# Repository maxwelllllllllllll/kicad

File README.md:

# kicad
 
Here's my dumb repo for projects I'm working on in Kicad. For the near term (and maybe forever), this is going to be entirely custom keyboard projects.

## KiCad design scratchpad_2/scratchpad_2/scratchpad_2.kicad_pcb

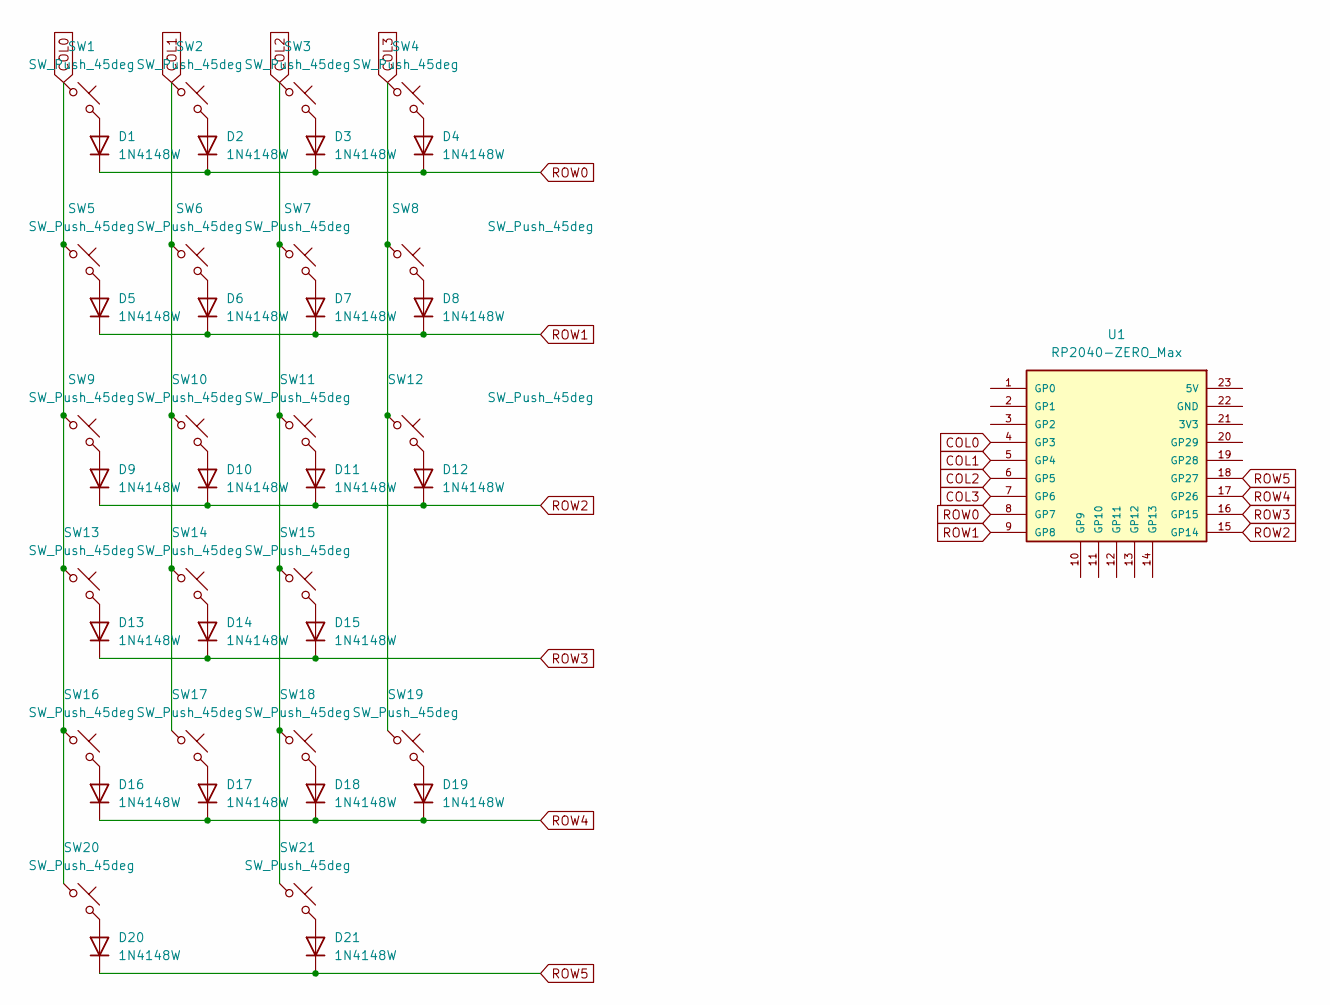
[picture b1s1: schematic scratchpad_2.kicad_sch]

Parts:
D1, D2, D3, D4, D5, D6, D7, D8, D9, D10, D11, D12, D13, D14, D15, D16, D17, D18, D19, D20, D21: 1N4148W; D_SOD-123
SW1, SW2, SW3, SW4, SW5, SW6, SW7, SW8, SW9, SW10, SW11, SW13, SW14, SW15, SW16, SW17, SW18, SW21: SW_Push_45deg; MX-Hotswap-1U
SW12, SW19, SW20: SW_Push_45deg; MX-Hotswap-2U-ReversedStabilizers
U1: RP2040-ZERO_Max; MODULE_RP2040-ZERO

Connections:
COL0: SW1.1, SW5.1, SW9.1, SW13.1, SW16.1, SW20.1, U1.4 (GP3)
COL1: SW2.1, SW6.1, SW10.1, SW14.1, SW17.1, U1.5 (GP4)
COL2: SW3.1, SW7.1, SW11.1, SW15.1, SW18.1, SW21.1, U1.6 (GP5)
COL3: SW4.1, SW8.1, SW12.1, SW19.1, U1.7 (GP6)
unnamed: D1.2 (A), SW1.2
unnamed: D2.2 (A), SW2.2
unnamed: D3.2 (A), SW3.2
unnamed: D4.2 (A), SW4.2
unnamed: D5.2 (A), SW5.2
unnamed: D6.2 (A), SW6.2
unnamed: D7.2 (A), SW7.2
unnamed: D8.2 (A), SW8.2
unnamed: D9.2 (A), SW9.2
unnamed: D10.2 (A), SW10.2
unnamed: D11.2 (A), SW11.2
unnamed: D12.2 (A), SW12.2
unnamed: D13.2 (A), SW13.2
unnamed: D14.2 (A), SW14.2
unnamed: D15.2 (A), SW15.2
unnamed: D16.2 (A), SW16.2
unnamed: D17.2 (A), SW17.2
unnamed: D18.2 (A), SW18.2
unnamed: D19.2 (A), SW19.2
unnamed: D20.2 (A), SW20.2
unnamed: D21.2 (A), SW21.2
ROW0: D1.1 (K), D2.1 (K), D3.1 (K), D4.1 (K), U1.8 (GP7)
ROW1: D5.1 (K), D6.1 (K), D7.1 (K), D8.1 (K), U1.9 (GP8)
ROW2: D9.1 (K), D10.1 (K), D11.1 (K), D12.1 (K), U1.15 (GP14)
ROW3: D13.1 (K), D14.1 (K), D15.1 (K), U1.16 (GP15)
ROW4: D16.1 (K), D17.1 (K), D18.1 (K), D19.1 (K), U1.17 (GP26)
ROW5: D20.1 (K), D21.1 (K), U1.18 (GP27)

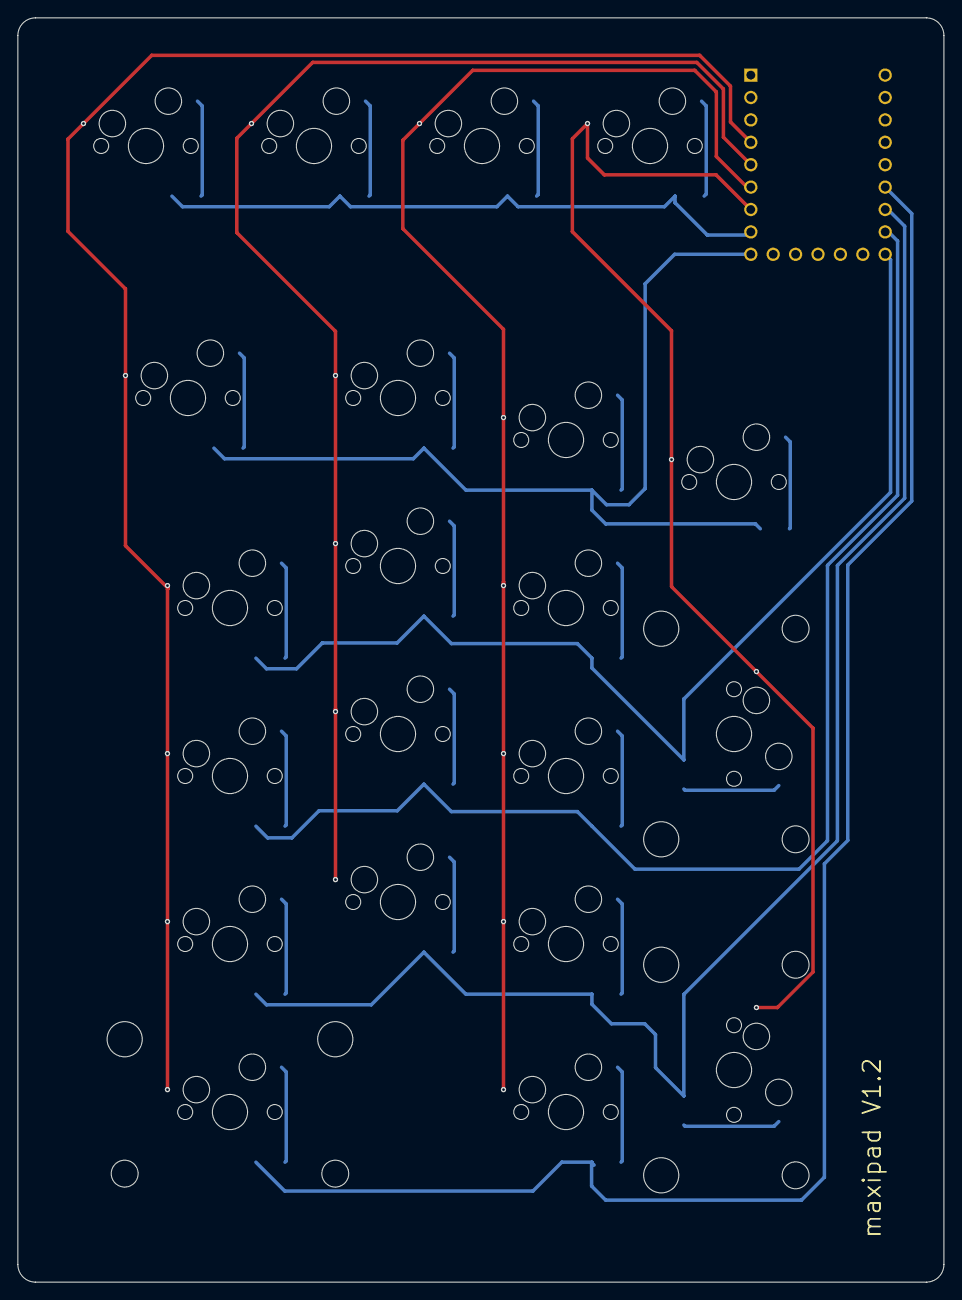
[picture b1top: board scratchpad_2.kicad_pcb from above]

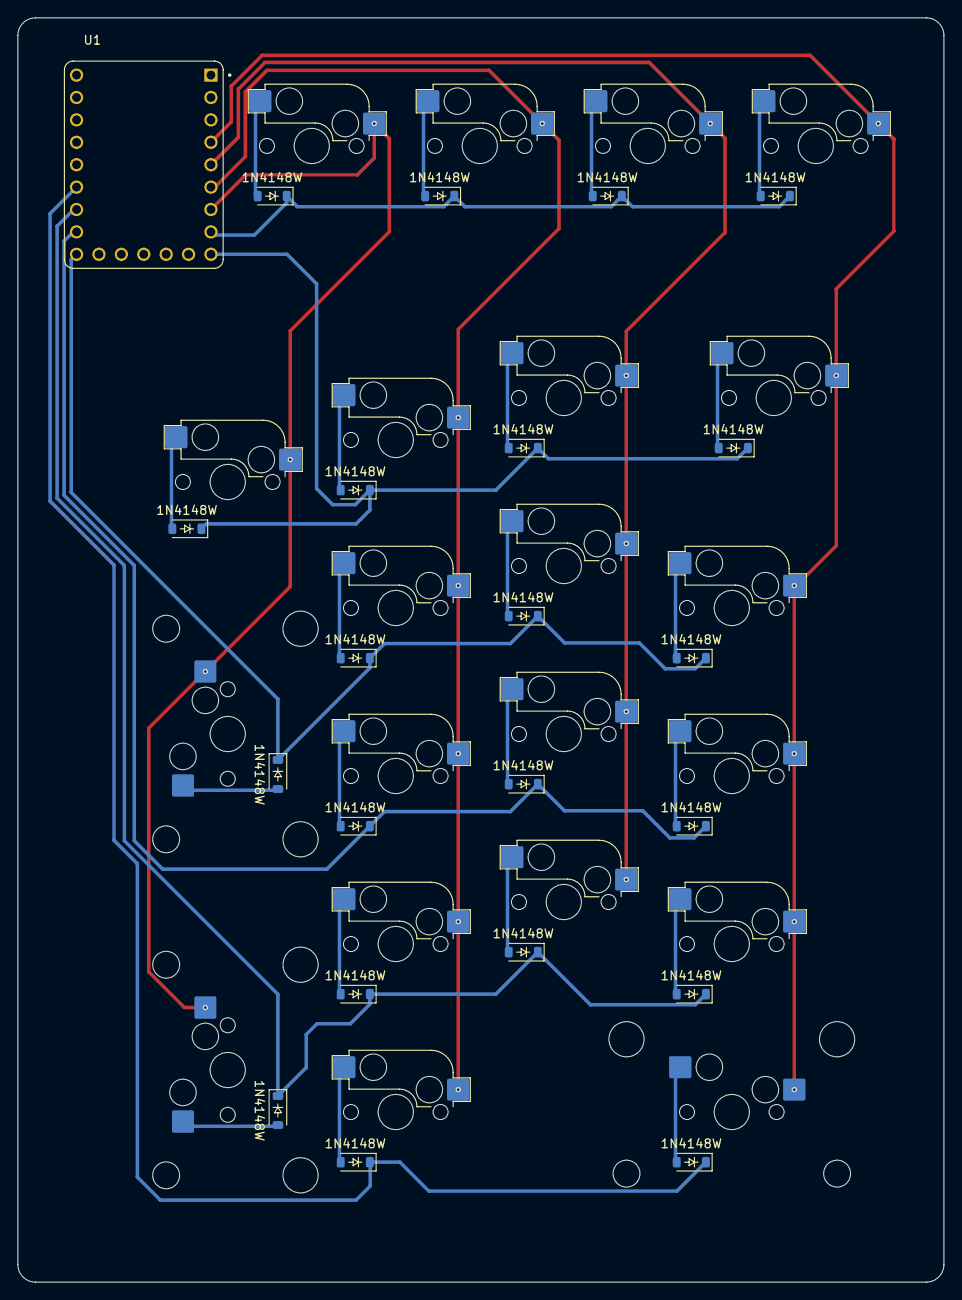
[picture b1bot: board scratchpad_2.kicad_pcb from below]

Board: 2 copper layers, 105.0 x 143.3 mm, 43 parts (43 on the bottom side), 31 nets.

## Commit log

2024-11-19 First loadout
2024-11-19 updated schem and pcb
2024-11-19 a little more routing
2024-11-20 only a few traces left
2024-11-21 updated switch footprints
2024-11-21 just about done
2024-11-21 Add graphics
2024-11-22 Ready to Build
2024-11-22 Add KLE image
    https://gist.github.com/maxwelllllllllllll/b43787d300a2b5dd510d8db41ba435d7
2024-11-22 Updated KLE image
    https://gist.github.com/maxwelllllllllllll/b43787d300a2b5dd510d8db41ba435d7
2024-11-22 Added MX_V2 libs
2024-11-22 small changes to production files
2024-11-22 scratchpad startup
2024-11-22 added schematic lib
2024-11-22 Added random keyboard parts lib
2024-11-22 Add keyboard parts lib
2024-11-22 gitignore MX_V2
2024-11-23 updated scratch
2024-11-24 update layout for pcb
2024-11-25 scratchpad complete
2024-11-27 scratchpad 2 done
2024-11-27 chamfered edge cuts
2024-11-27 added 3d models
